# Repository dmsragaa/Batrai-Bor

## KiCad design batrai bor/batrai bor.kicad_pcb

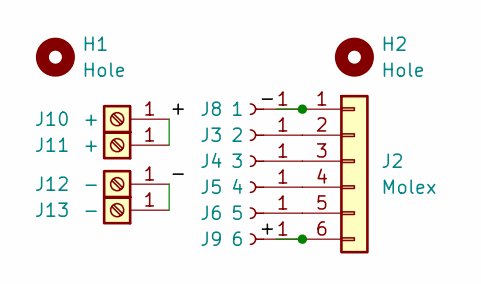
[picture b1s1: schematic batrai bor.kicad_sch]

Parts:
H1, H2: Hole; MountingHole_2.2mm_M2_DIN965_Pad
J2: Molex; JST_XH_S6B-XH-A-1_1x06_P2.50mm_Horizontal
J3: 2; Pin_D1.3mm_L11.0mm
J4: 3; Pin_D1.3mm_L11.0mm
J5: 4; Pin_D1.3mm_L11.0mm
J6: 5; Pin_D1.3mm_L11.0mm
J8: 1; Pin_D1.3mm_L11.0mm
J9: 6; Pin_D1.3mm_L11.0mm
J10, J11: +; Pin_D1.3mm_L10.0mm_W3.5mm_Flat
J12, J13: -; Pin_D1.3mm_L10.0mm_W3.5mm_Flat

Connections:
/+: J2.6, J9.1, J10.1, J11.1
/-: J2.1, J8.1, J12.1, J13.1
unnamed: J2.2, J3.1
unnamed: J2.3, J4.1
unnamed: J2.4, J5.1
unnamed: J2.5, J6.1

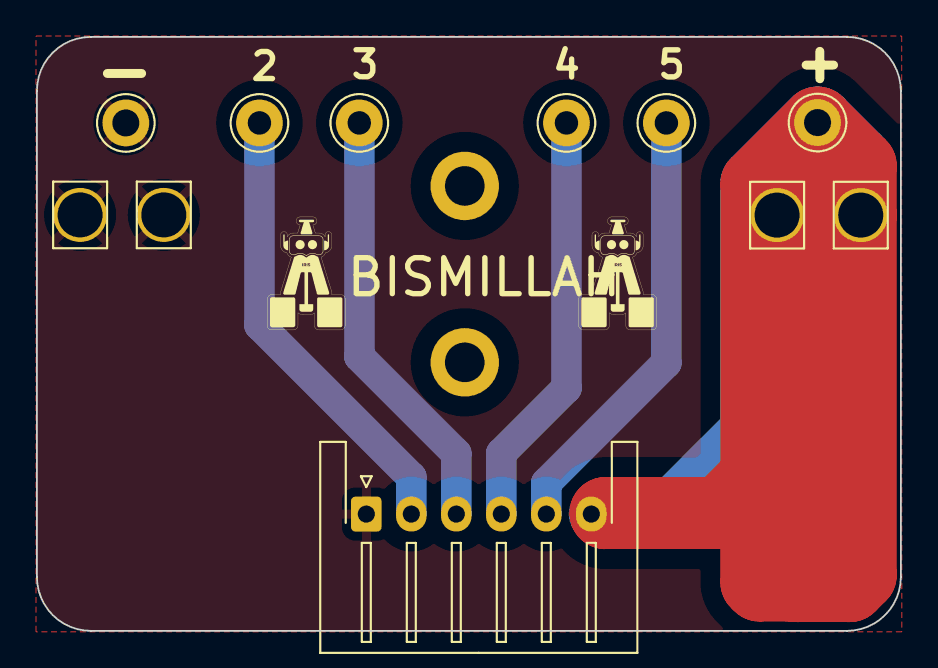
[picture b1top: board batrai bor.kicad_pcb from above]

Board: 2 copper layers, 48.0 x 33.0 mm, 13 parts (0 on the bottom side), 6 nets.

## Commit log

2024-04-03 V.4.1
